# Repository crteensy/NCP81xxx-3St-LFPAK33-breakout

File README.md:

# NCP81xxx-3St-LFPAK33-breakout
Breakout board for gate drivers like NCP81253 or NCP81161 with 3-state PWM input and FETs in LFPAK33 like the PSMN1R8-30MLH

## Purpose
The purpose of this breakout board is to simplify BLDC ESC development by separating MCU and power stage on different boards. That way a proven gate driver/FET power stage can be used with different MCUs, or working code can be used with different power stages.

## Features
Inputs:
- active low enable for all gate drivers
- high side and low side inputs for each gate driver, wired to a pair of pull-up resistors to generate 3-state PWM with either) two plain open-drain outputs or) one plain open drain output for the low side and one resistive open drain output for the high side.

You can choose to connect the phase feedback voltage dividers to ground on J2 using a jumper or to bias them with an external voltage supply (1V2 has worked here). This feature was necessary to implement BLDC control with an ADC whose input range doesn't extend below ground (this was the case with PSoC6).

Outputs:
- Motor connections of course
- phase feedback voltage divider output.

## PCB design rules (if you want to get them made):
- Layers: 2
- smallest drill: 0.3 mm
- track width/spacing: 0.2 mm
so nothing special at all.

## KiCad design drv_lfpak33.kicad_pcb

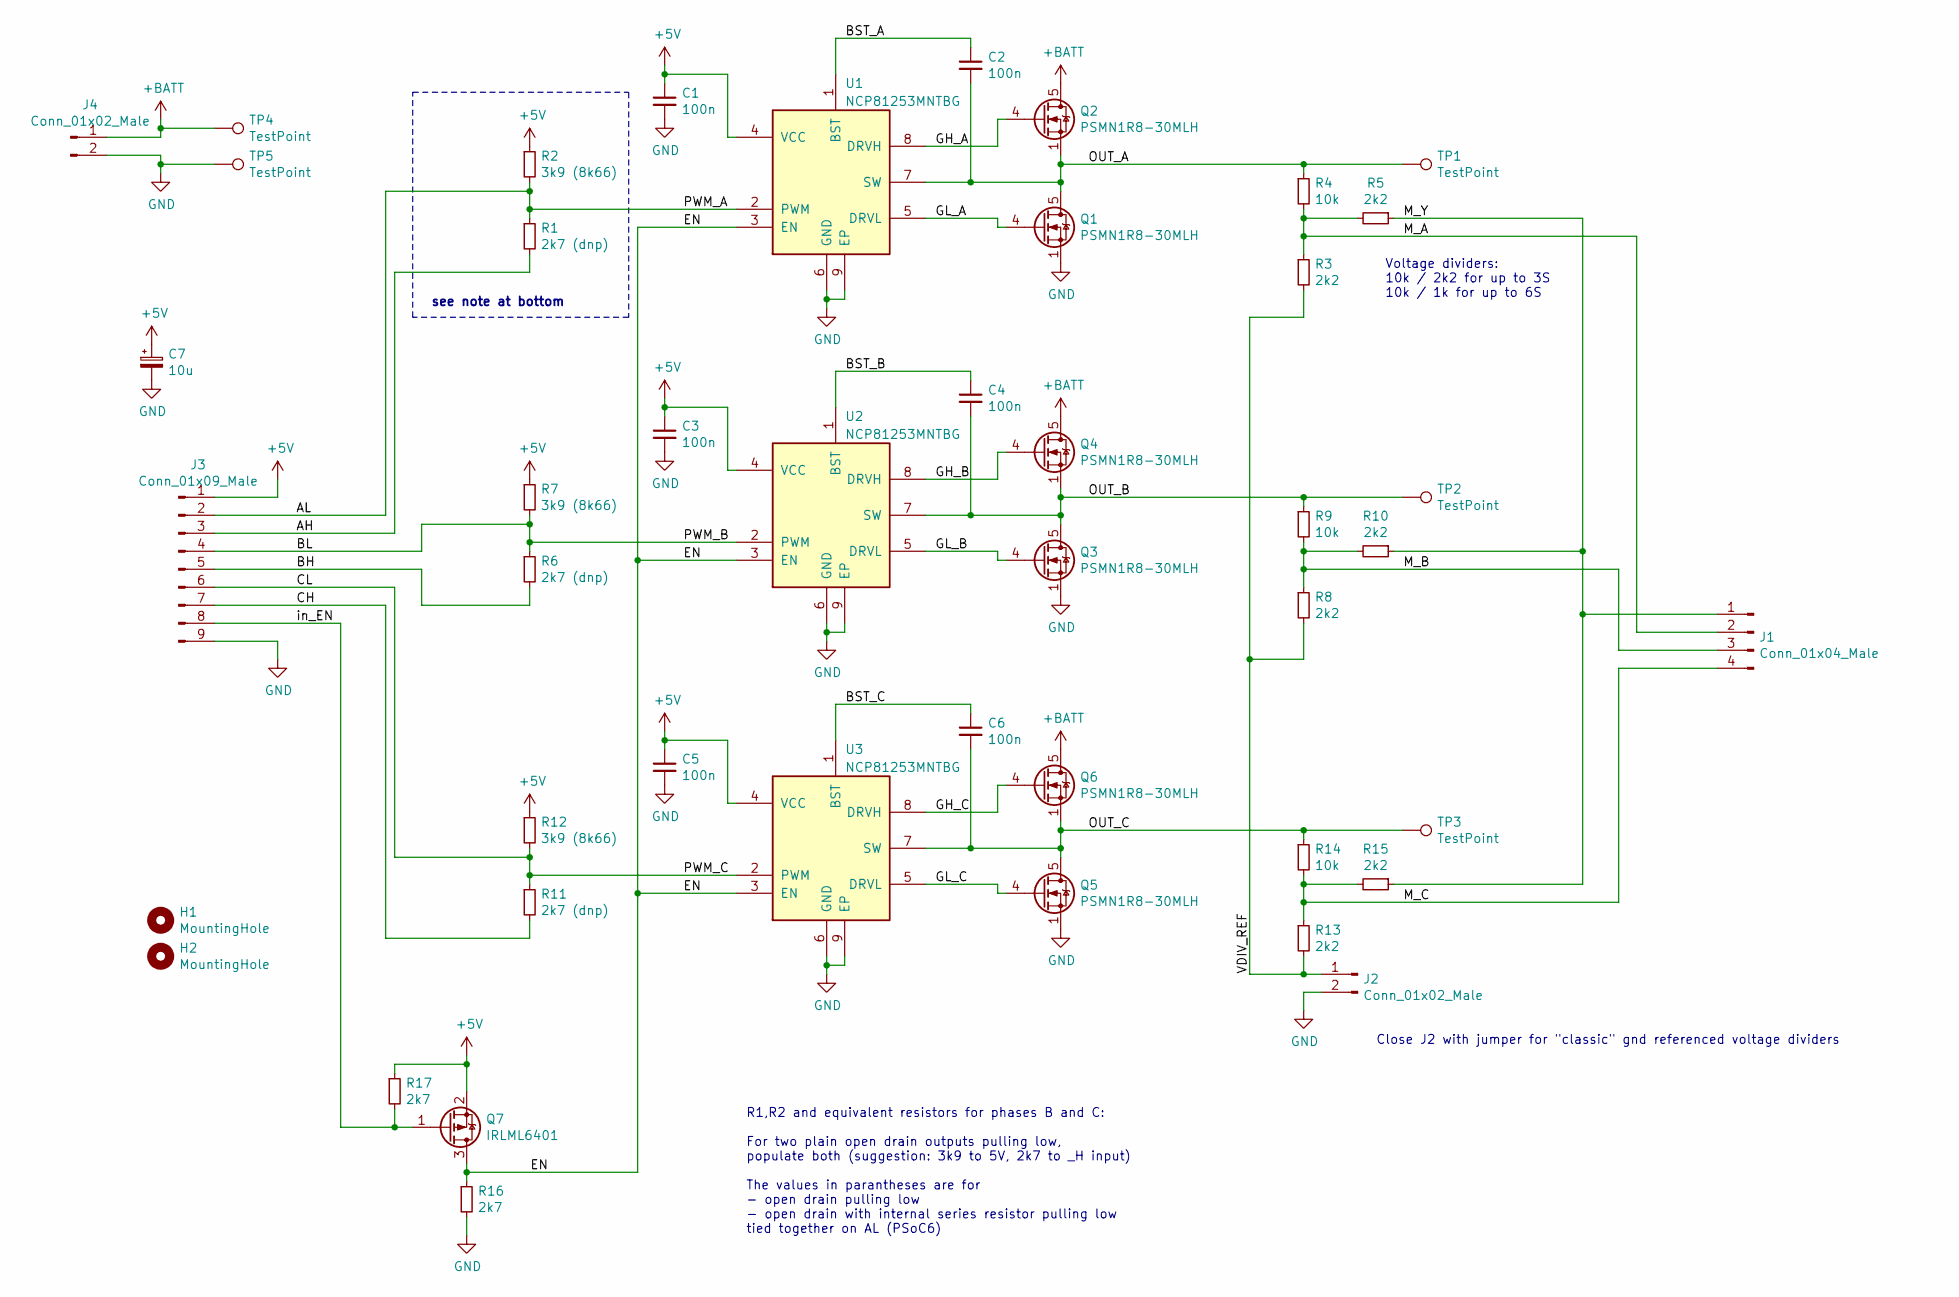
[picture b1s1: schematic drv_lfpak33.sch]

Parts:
C1, C2, C3, C4, C5, C6: 100n; C_0603_1608Metric
C7: 10u; CP_EIA-3216-18_Kemet-A
H1, H2: MountingHole; MountingHole_3.2mm_M3
J1: Conn_01x04_Male; PinHeader_1x04_P2.54mm_Vertical
J2, J4: Conn_01x02_Male; PinHeader_1x02_P2.54mm_Vertical
J3: Conn_01x09_Male; PinHeader_1x09_P2.54mm_Vertical
Q1, Q2, Q3, Q4, Q5, Q6: PSMN1R8-30MLH; LFPAK33
Q7: IRLML6401; SOT-23
R1, R6, R11: 2k7 (dnp); R_0603_1608Metric
R2, R7, R12: 3k9 (8k66); R_0603_1608Metric
R3, R5, R8, R10, R13, R15: 2k2; R_0603_1608Metric
R4, R9, R14: 10k; R_0603_1608Metric
R16, R17: 2k7; R_0603_1608Metric
TP1, TP2, TP3: TestPoint; TestPoint_Pad_2.0x2.0mm
TP4, TP5: TestPoint; TestPoint_Pad_3.0x3.0mm
U1, U2, U3: NCP81253MNTBG; DFN-8-1EP_2x2mm_P0.5mm_EP0.9x1.3mm

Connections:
+5V: C1.1, C3.1, C5.1, C7.1, J3.1, Q7.2 (S), R2.1, R7.1, R12.1, R17.1, U1.4 (VCC), U2.4 (VCC), U3.4 (VCC)
+BATT: J4.1, Q2.5 (D), Q4.5 (D), Q6.5 (D), TP4.1
/AH: J3.3, R1.2
/AL: J3.2, R1.1, R2.2, U1.2 (PWM)
/BH: J3.5, R6.2
/BL: J3.4, R6.1, R7.2, U2.2 (PWM)
/BST_A: C2.1, U1.1 (BST)
/BST_B: C4.1, U2.1 (BST)
/BST_C: C6.1, U3.1 (BST)
/CH: J3.7, R11.2
/CL: J3.6, R11.1, R12.2, U3.2 (PWM)
/EN: Q7.3 (D), R16.1, U1.3 (EN), U2.3 (EN), U3.3 (EN)
/GH_A: Q2.4 (G), U1.8 (DRVH)
/GH_B: Q4.4 (G), U2.8 (DRVH)
/GH_C: Q6.4 (G), U3.8 (DRVH)
/GL_A: Q1.4 (G), U1.5 (DRVL)
/GL_B: Q3.4 (G), U2.5 (DRVL)
/GL_C: Q5.4 (G), U3.5 (DRVL)
/M_A: J1.2, R3.1, R4.2, R5.2
/M_B: J1.3, R8.1, R9.2, R10.2
/M_C: J1.4, R13.1, R14.2, R15.2
/M_Y: J1.1, R5.1, R10.1, R15.1
/OUT_A: C2.2, Q1.5 (D), Q2.1 (S), Q2.2 (S), Q2.3 (S), R4.1, TP1.1, U1.7 (SW)
/OUT_B: C4.2, Q3.5 (D), Q4.1 (S), Q4.2 (S), Q4.3 (S), R9.1, TP2.1, U2.7 (SW)
/OUT_C: C6.2, Q5.5 (D), Q6.1 (S), Q6.2 (S), Q6.3 (S), R14.1, TP3.1, U3.7 (SW)
/VDIV_REF: J2.1, R3.2, R8.2, R13.2
/in_EN: J3.8, Q7.1 (G), R17.2
GND: C1.2, C3.2, C5.2, C7.2, J2.2, J3.9, J4.2, Q1.1 (S), Q1.2 (S), Q1.3 (S), Q3.1 (S), Q3.2 (S), Q3.3 (S), Q5.1 (S), Q5.2 (S), Q5.3 (S), R16.2, TP5.1, U1.6 (GND), U1.9 (EP), U2.6 (GND), U2.9 (EP), U3.6 (GND), U3.9 (EP)

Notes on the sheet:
see note at bottom
R1,R2 and equivalent resistors for phases B and C: For two plain open drain outputs pulling low, populate both (suggestion: 3k9 to 5V, 2k7 to _H input) The values in parantheses are for - open drain pulling low - open drain with internal series resistor pulling low tied together on AL (PSoC6)
Close J2 with jumper for "classic" gnd referenced voltage dividers
Voltage dividers: 10k / 2k2 for up to 3S 10k / 1k for up to 6S

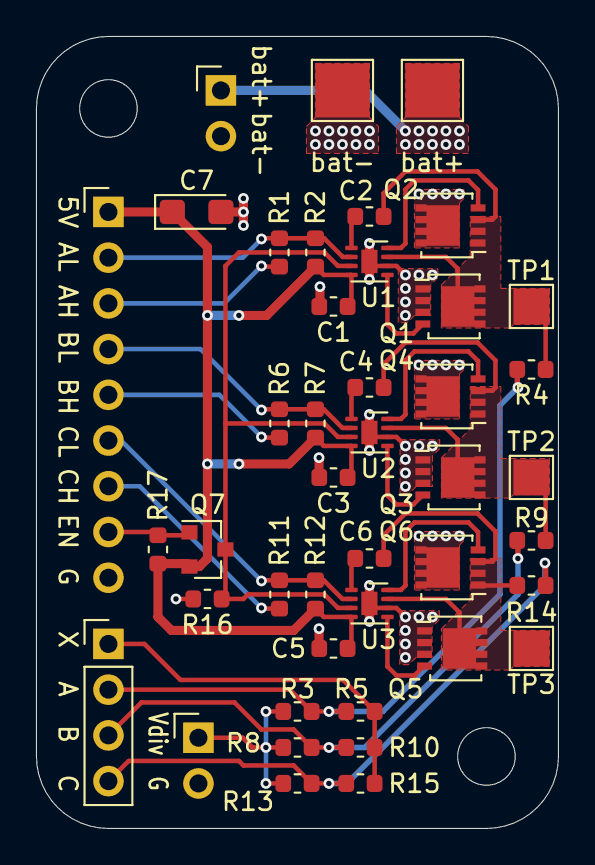
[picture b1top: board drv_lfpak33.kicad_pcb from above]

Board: 2 copper layers, 29.0 x 44.0 mm, 45 parts (0 on the bottom side), 28 nets.

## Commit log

2021-01-28 initial kicad project commit
2021-02-13 update schematic: correct pull resistor values
2021-02-14 update bottom silkscreen
2021-02-23 add mounting holes
2021-02-23 update 3d view and schematic pdf
